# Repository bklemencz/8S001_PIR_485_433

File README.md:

# 8S001_PIR_485_433
 STM8S001 Motion Sensor To RS485 & EV1527

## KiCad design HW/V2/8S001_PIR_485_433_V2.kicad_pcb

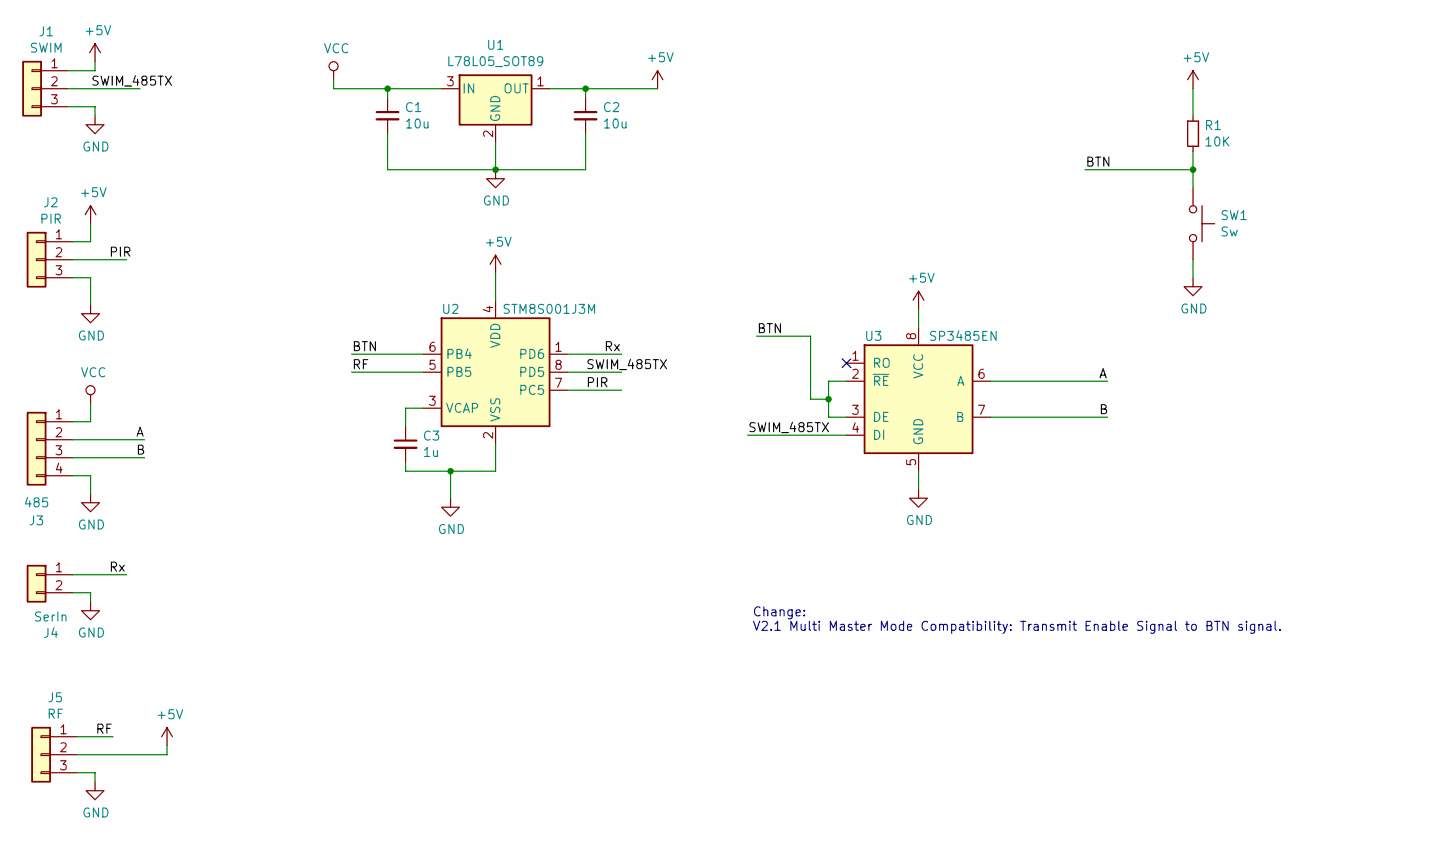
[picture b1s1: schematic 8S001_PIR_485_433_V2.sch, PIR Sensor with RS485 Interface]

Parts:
C1, C2: 10u; C_1206_3216Metric
C3: 1u; C_0805_2012Metric
J1: SWIM; Pin_Header_Straight_1x03_Pitch2.54mm
J2: PIR; Pin_Header_Straight_1x03_Pitch2.54mm
J3: 485; PinHeader_1x04_P2.54mm_Vertical
J4: SerIn; PinHeader_1x02_P2.54mm_Vertical
J5: RF; SYN115_Mod
R1: 10K; R_0805_2012Metric
SW1: Sw; SW_SPST_CK_RS282G05A3
U1: L78L05_SOT89; SOT-89-3
U2: STM8S001J3M; SOIC-8_3.9x4.9mm_P1.27mm
U3: SP3485EN; SOIC-8_3.9x4.9mm_P1.27mm

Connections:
+5V: C2.1, J1.1, J2.1, J5.2, R1.1, U1.1 (OUT), U2.4 (VDD), U3.8 (VCC)
/A: J3.2, U3.6 (A)
/B: J3.3, U3.7 (B)
/BTN: R1.2, SW1.1, U2.6 (PB4), U3.2 (~RE~), U3.3 (DE)
/PIR: J2.2, U2.7 (PC5)
/RF: J5.1, U2.5 (PB5)
/Rx: J4.1, U2.1 (PD6)
/SWIM_485TX: J1.2, U2.8 (PD5), U3.4 (DI)
GND: C1.2, C2.2, C3.2, J1.3, J2.3, J3.4, J4.2, J5.3, SW1.2, U1.2 (GND), U2.2 (VSS), U3.5 (GND); also elsewhere on the board
unnamed: C3.1, U2.3 (VCAP)
VCC: C1.1, J3.1, U1.3 (IN)

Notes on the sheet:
Change: V2.1 Multi Master Mode Compatibility: Transmit Enable Signal to BTN signal.

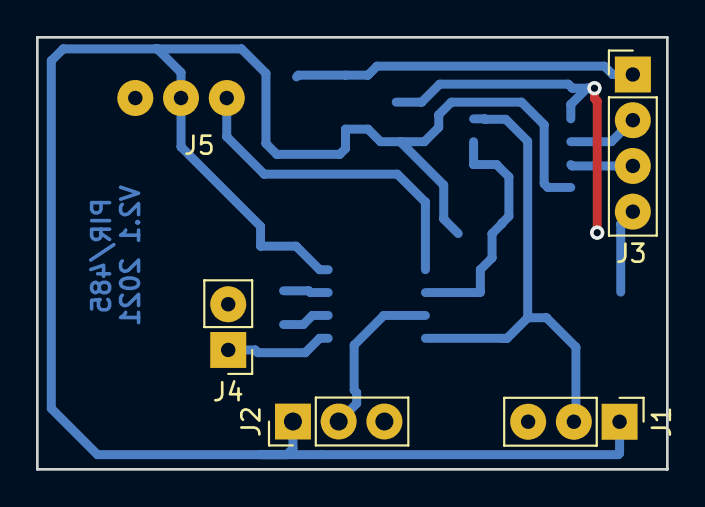
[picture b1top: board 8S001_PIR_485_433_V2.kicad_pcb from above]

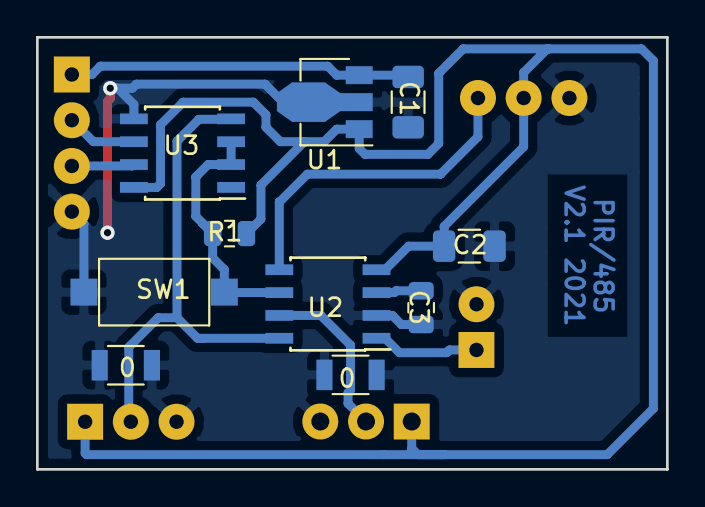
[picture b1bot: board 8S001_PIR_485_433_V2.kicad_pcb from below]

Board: 2 copper layers, 35.0 x 24.0 mm, 15 parts (10 on the bottom side), 11 nets.

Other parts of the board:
0, 0#2: R_1206

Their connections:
GND: 0.1, 0.2, 0#2.1, 0#2.2; also elsewhere on the board

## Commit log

2021-02-04 V2.1 HW
    MAX485 Data Enable wired to BTN signal, now 485 transmitter can be disabled for multimaster mode
